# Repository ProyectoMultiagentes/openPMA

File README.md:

# openPMA: Plataforma experimental multi-agentes
Repositorio de la plataforma experimental multi-agentes
## Descripcion de la plataforma

La plataforma experimental consta de tres partes fundamentales:

- Superficie de navegacion modular
- Trayectoria de navegacion
- Flota de robots mobiles

La superficie es de goma eva, para esta aplicacion se utiliza en color negro, y tiene la capacidad de montarse y desmontarse con facilidad.
Por otra parte, la trayectoria de navegacion corresponde a un segmente continuo, pintado en color blanco sobre la superficie.
Finalmente, la flota de robots moviles esta compuesta por robots identicos, de traccion diferencial (DDMR), los cuales, tienen la capacidad de seguir trayectorias abiertas o cerradas; mantener una distancia fija respecto a su robot predecesor; seguir referencias de velocidad; comunicarse con otros agentes utilizando el protocolo de comunicacion UDP a traves de un punto de acceso WiFi; entre otras.

## Prueba de Funcionamiento

En este video se realiza una prueba de funcionamiento de la plataforma experimental. Ademas, muestra la capacidad de los robots de navegar de forma cooperativa. El video completo se puede ver en:
https://youtu.be/nR3WdcdglEQ

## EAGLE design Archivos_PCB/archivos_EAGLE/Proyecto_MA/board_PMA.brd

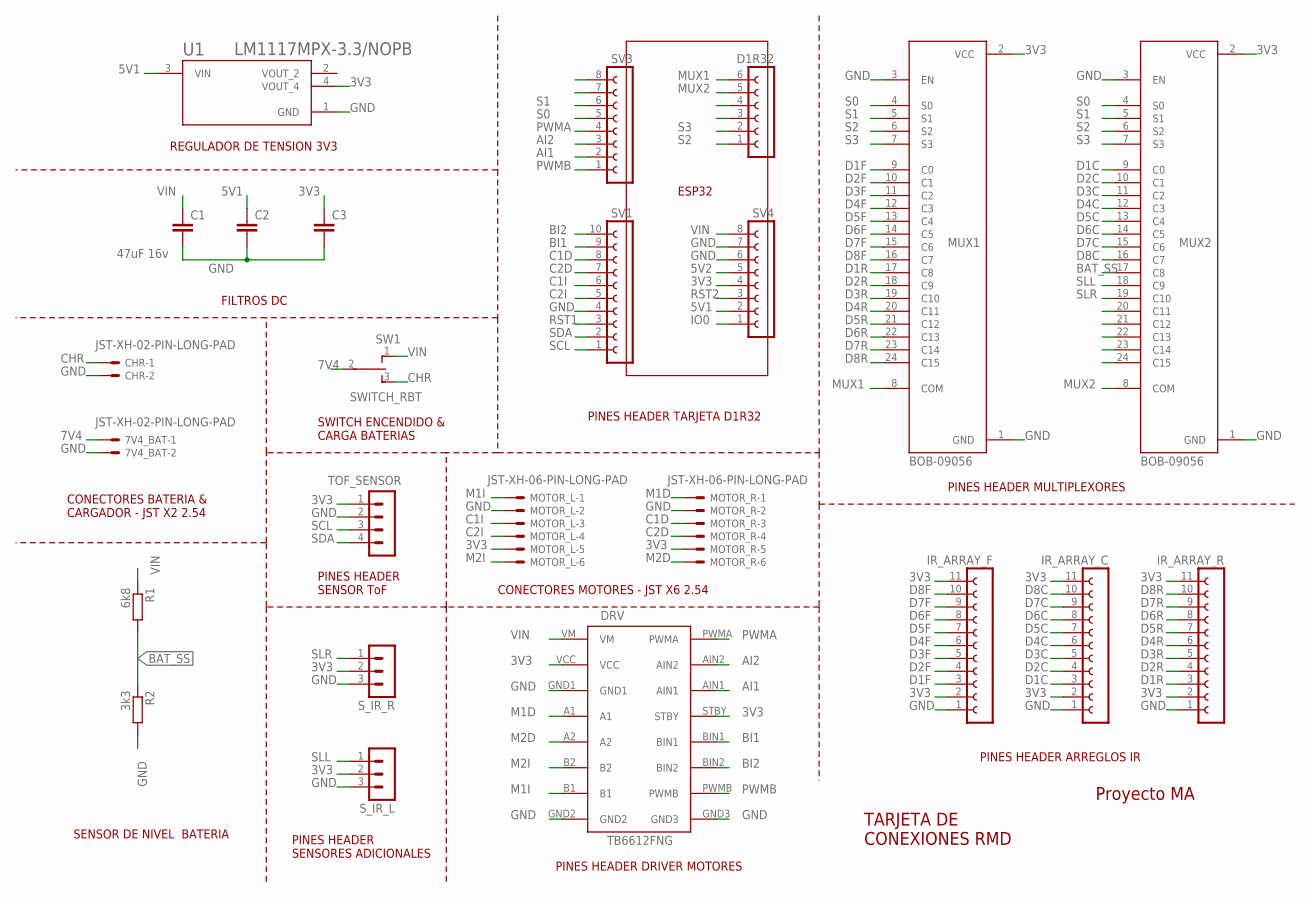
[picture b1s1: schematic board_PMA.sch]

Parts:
7V4_BAT: JST-XH-02-PIN-LONG-PAD; JST-XH-02-PACKAGE-LONG-PAD
C1: 47uF 16v; C1206K
C2, C3: C-EUC1206K; C1206K
CHR: JST-XH-02-PIN-LONG-PAD; JST-XH-02-PACKAGE-LONG-PAD
D1R32: FE06-1; FE06
DRV: TB6612FNG
IR_ARRAY_C: FE11-1; FE11
IR_ARRAY_F: FE11-1; FE11
IR_ARRAY_R: FE11-1; FE11
MOTOR_L: JST-XH-06-PIN-LONG-PAD; JST-XH-06-PACKAGE-LONG-PAD
MOTOR_R: JST-XH-06-PIN-LONG-PAD; JST-XH-06-PACKAGE-LONG-PAD
MUX1, MUX2: BOB-09056; XDCR_BOB-09056
R1: 6k8; 0207/10
R2: 3k3; 0207/10
SV1: FE10-1; FE10
SV3, SV4: FE08-1; FE08
SW1: SWITCH_RBT; SW
S_IR_L: MA03-1
S_IR_R: MA03-1
TOF_SENSOR: MA04-1
U1: LM1117MPX-3.3/NOPB; VREG_LM1117MPX-3.3/NOPB

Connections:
3V3: C3.1, DRV.STBY, DRV.VCC, IR_ARRAY_C.2, IR_ARRAY_C.11, IR_ARRAY_F.2, IR_ARRAY_F.11, IR_ARRAY_R.2, IR_ARRAY_R.11, MOTOR_L.5, MOTOR_R.5, MUX1.2 (VCC), MUX2.2 (VCC), SV4.4, S_IR_L.2, S_IR_R.2, TOF_SENSOR.1, U1.4 (VOUT_4)
5V1: C2.1, SV4.2, U1.3 (VIN)
5V2: SV4.5
7V4: 7V4_BAT.1, SW1.2
AI1: DRV.AIN1, SV3.2
AI2: DRV.AIN2, SV3.3
BAT_SS: MUX2.17 (C8), R1.2, R2.1
BI1: DRV.BIN1, SV1.9
BI2: DRV.BIN2, SV1.10
C1D: MOTOR_R.3, SV1.8
C1I: MOTOR_L.3, SV1.6
C2D: MOTOR_R.4, SV1.7
C2I: MOTOR_L.4, SV1.5
CHR: CHR.1, SW1.3
D1C: IR_ARRAY_C.3, MUX2.9 (C0)
D1F: IR_ARRAY_F.3, MUX1.9 (C0)
D1R: IR_ARRAY_R.3, MUX1.17 (C8)
D2C: IR_ARRAY_C.4, MUX2.10 (C1)
D2F: IR_ARRAY_F.4, MUX1.10 (C1)
D2R: IR_ARRAY_R.4, MUX1.18 (C9)
D3C: IR_ARRAY_C.5, MUX2.11 (C2)
D3F: IR_ARRAY_F.5, MUX1.11 (C2)
D3R: IR_ARRAY_R.5, MUX1.19 (C10)
D4C: IR_ARRAY_C.6, MUX2.12 (C3)
D4F: IR_ARRAY_F.6, MUX1.12 (C3)
D4R: IR_ARRAY_R.6, MUX1.20 (C11)
D5C: IR_ARRAY_C.7, MUX2.13 (C4)
D5F: IR_ARRAY_F.7, MUX1.13 (C4)
D5R: IR_ARRAY_R.7, MUX1.21 (C12)
D6C: IR_ARRAY_C.8, MUX2.14 (C5)
D6F: IR_ARRAY_F.8, MUX1.14 (C5)
D6R: IR_ARRAY_R.8, MUX1.22 (C13)
D7C: IR_ARRAY_C.9, MUX2.15 (C6)
D7F: IR_ARRAY_F.9, MUX1.15 (C6)
D7R: IR_ARRAY_R.9, MUX1.23 (C14)
D8C: IR_ARRAY_C.10, MUX2.16 (C7)
D8F: IR_ARRAY_F.10, MUX1.16 (C7)
D8R: IR_ARRAY_R.10, MUX1.24 (C15)
GND: 7V4_BAT.2, C1.2, C2.2, C3.2, CHR.2, DRV.GND1, DRV.GND2, DRV.GND3, IR_ARRAY_C.1, IR_ARRAY_F.1, IR_ARRAY_R.1, MOTOR_L.2, MOTOR_R.2, MUX1.1 (GND), MUX1.3 (EN), MUX2.1 (GND), MUX2.3 (EN), R2.2, SV1.4, SV4.6, SV4.7, S_IR_L.3, S_IR_R.3, TOF_SENSOR.2, U1.1 (GND)
IO0: SV4.1
M1D: DRV.A1, MOTOR_R.1
M1I: DRV.B1, MOTOR_L.1
M2D: DRV.A2, MOTOR_R.6
M2I: DRV.B2, MOTOR_L.6
MUX1: D1R32.6, MUX1.8 (COM)
MUX2: D1R32.5, MUX2.8 (COM)
PWMA: DRV.PWMA, SV3.4
PWMB: DRV.PWMB, SV3.1
RST1: SV1.3
RST2: SV4.3
S0: MUX1.4 (S0), MUX2.4 (S0), SV3.5
S1: MUX1.5 (S1), MUX2.5 (S1), SV3.6
S2: D1R32.1, MUX1.6 (S2), MUX2.6 (S2)
S3: D1R32.2, MUX1.7 (S3), MUX2.7 (S3)
SCL: SV1.1, TOF_SENSOR.3
SDA: SV1.2, TOF_SENSOR.4
SLL: MUX2.18 (C9), S_IR_L.1
SLR: MUX2.19 (C10), S_IR_R.1
VIN: C1.1, DRV.VM, R1.1, SV4.8, SW1.1

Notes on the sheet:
ESP32
PINES HEADER TARJETA D1R32
REGULADOR DE TENSION 3V3
FILTROS DC
CONECTORES BATERIA & CARGADOR - JST X2 2.54
SENSOR DE NIVEL BATERIA
PINES HEADER SENSORES ADICIONALES
PINES HEADER DRIVER MOTORES
PINES HEADER SENSOR ToF
CONECTORES MOTORES - JST X6 2.54
SWITCH ENCENDIDO & CARGA BATERIAS
PINES HEADER ARREGLOS IR
PINES HEADER MULTIPLEXORES
TARJETA DE CONEXIONES RMD
Proyecto MA

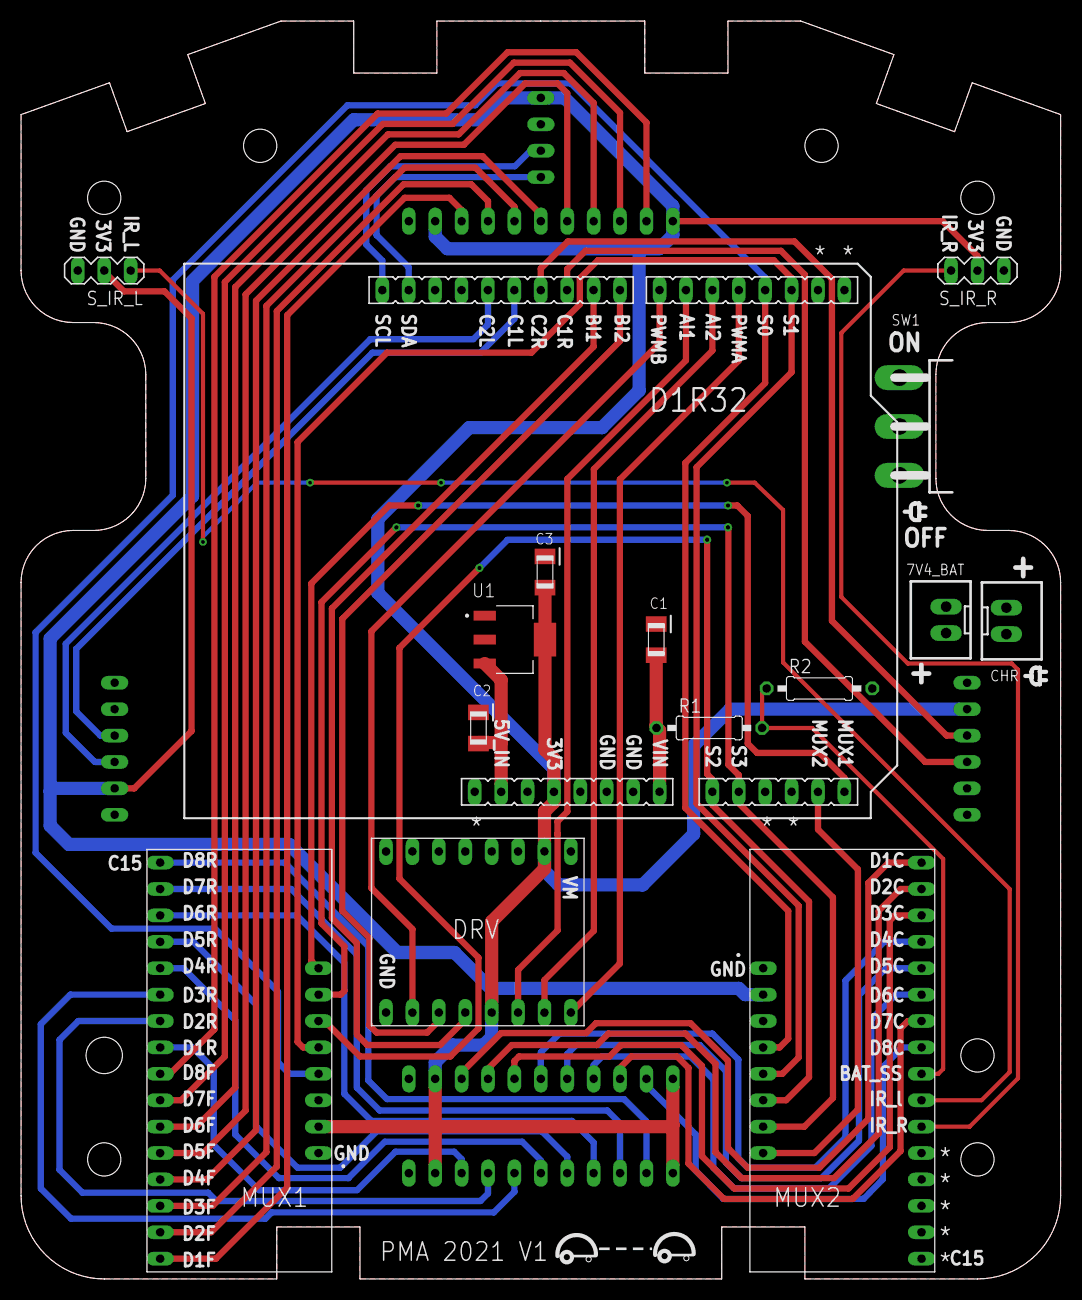
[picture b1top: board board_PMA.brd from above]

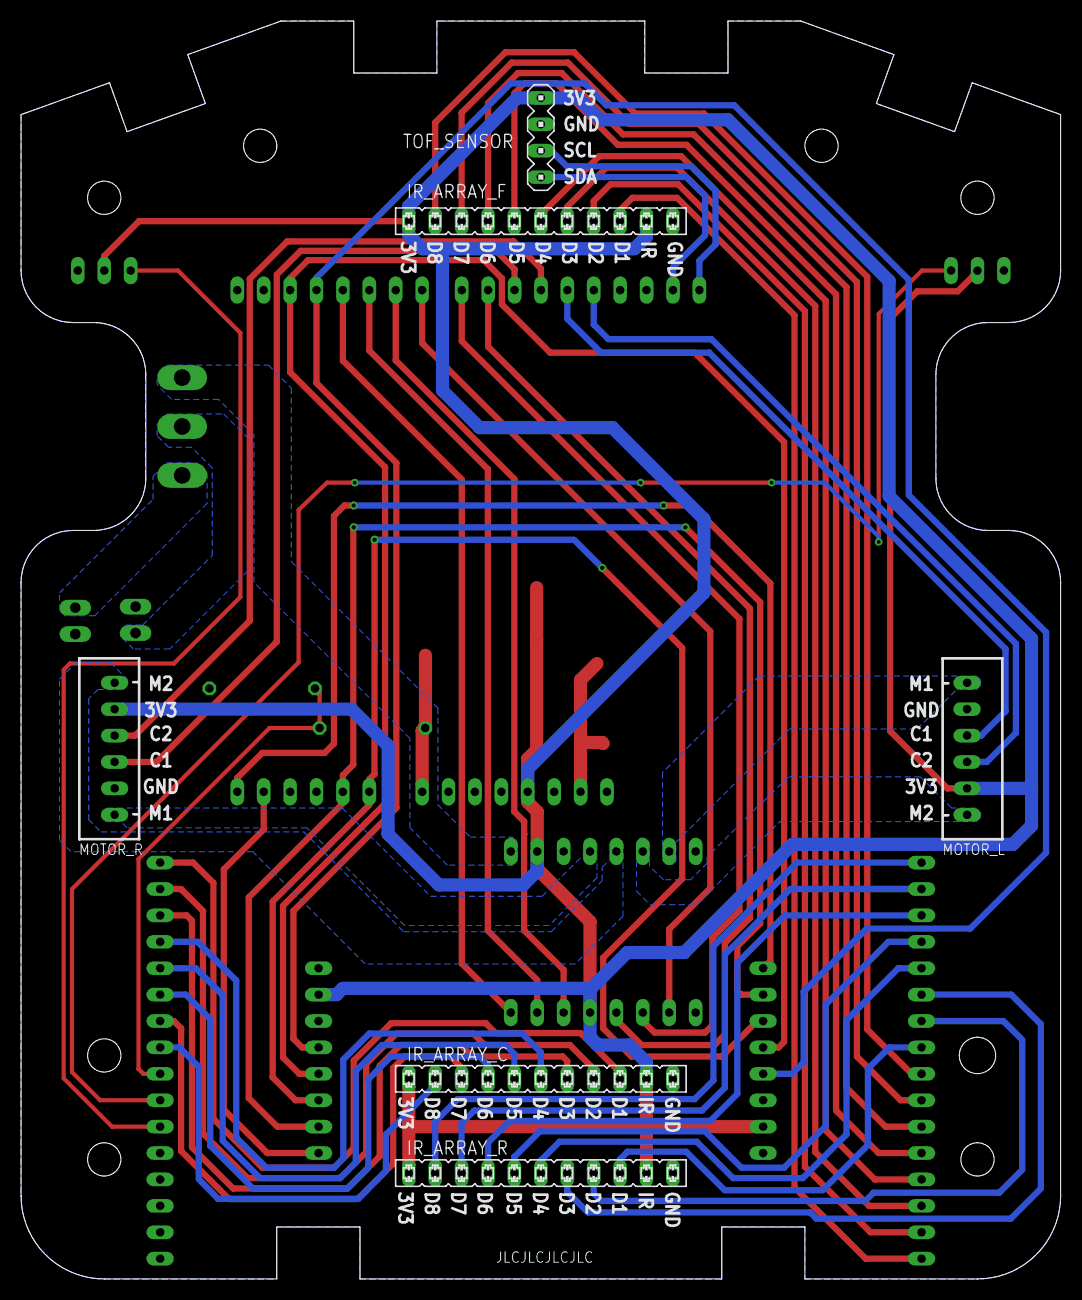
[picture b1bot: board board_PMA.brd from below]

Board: 2 copper layers, 100.0 x 121.0 mm, 24 parts (2 on the bottom side), 55 nets.

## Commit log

2021-09-12 Subida de códigos de prueba
2021-09-12 Se agrega descripción y comentarios
2021-09-12 Se agrega descripción y comentarios
    Se cambio el nombre de las variables "Velocidad_motor_izq"/"Velocidad_motor_der" por un nombre más apropiado "PWM_motor_izq"/"PWM_motor_der"
2021-12-01 Add files via upload
    se sube código PID
2022-01-05 Se agregan códigos actualizados
    Códigos actualizados para realizar pruebas a los sensores y actuadores del robot móvil diferencia (DDMR)
2022-01-05 Se agregan codigos de pruebas
    Codigos de pueba actualizados, para los sensores y actuadores del DDMR
2022-01-05 Se suben imagenes
